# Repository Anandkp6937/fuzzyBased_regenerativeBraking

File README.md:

<h1 style="font-weight:bold">fuzzy logic based regenrative braking system</h1>

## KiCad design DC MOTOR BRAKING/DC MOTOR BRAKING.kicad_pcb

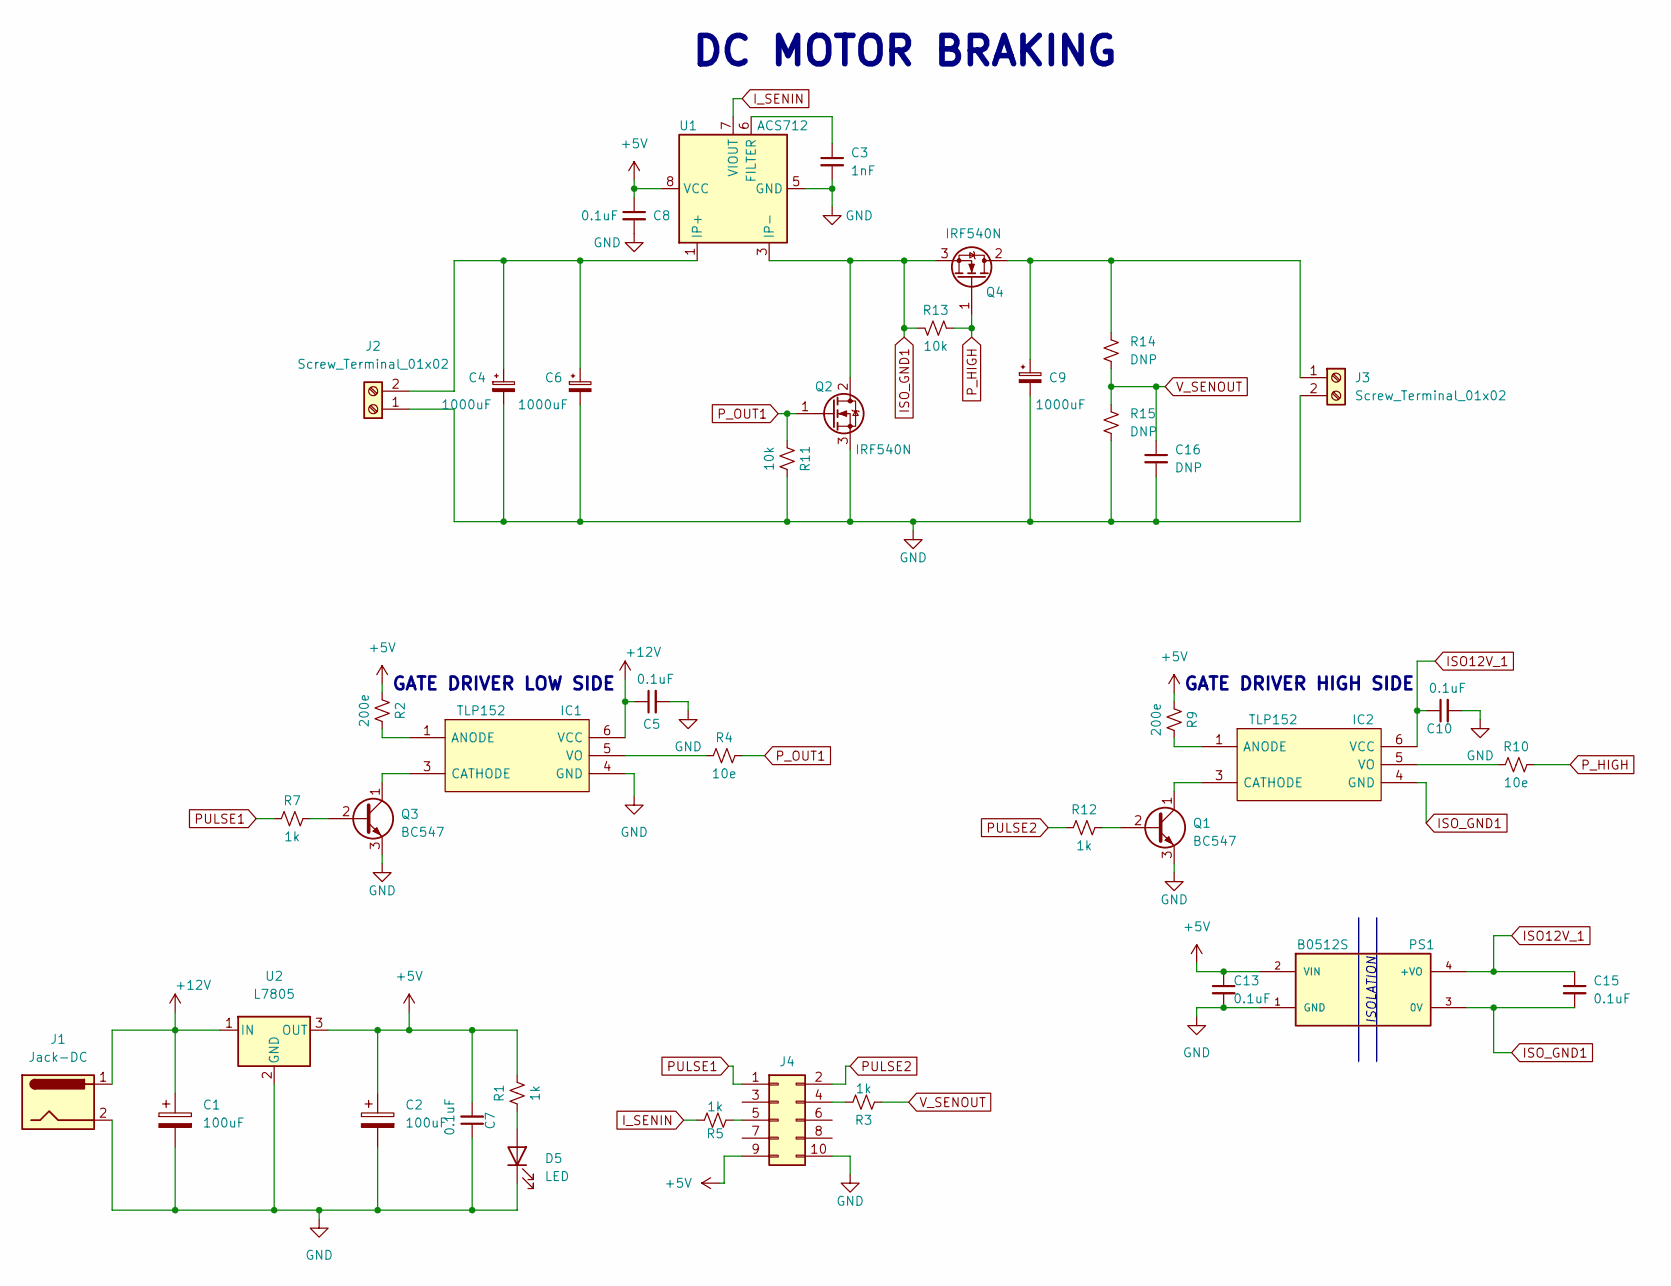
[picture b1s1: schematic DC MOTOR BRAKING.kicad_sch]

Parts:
C1: 100uF; CP_Radial_D6.3mm_P2.50mm
C2: 100uF; CP_Radial_D5.0mm_P2.50mm
C3: 1nF; C_0805_2012Metric_Pad1.18x1.45mm_HandSolder
C4, C6, C9: 1000uF; CP_Radial_D10.0mm_P5.00mm
C5, C7, C10, C13, C15: 0.1uF; C_Disc_D5.1mm_W3.2mm_P5.00mm
C8: 0.1uF; C_0805_2012Metric_Pad1.18x1.45mm_HandSolder
C16: DNP; C_Disc_D5.0mm_W2.5mm_P2.50mm
D5: LED; LED_D5.0mm
IC1, IC2: TLP152; SO-5_4.4x3.6mm_P1.27mm; Manufacturer_Part_Number TLP152
J1: Jack-DC; BarrelJack_Horizontal
J2, J3: Screw_Terminal_01x02; TerminalBlock_bornier-2_P5.08mm
J4: Conn_02x05_Odd_Even; IDC-Header_2x05_P2.54mm_Vertical
PS1: B0512S; CONV_B0512S-1WR3; PARTREV 2018.06.29-A/2
Q1, Q3: BC547; TO-92
Q2, Q4: IRF540N; TO-220
R1, R3, R5, R7, R12: 1k; 0.25W_resistor
R2, R9: 200e; 0.25W_resistor
R4, R10: 10e; 0.25W_resistor
R11, R13: 10k; 0.25W_resistor
R14, R15: DNP; 0.25W_resistor
U1: ACS712; SOIC-8_3.9x4.9mm_P1.27mm
U2: L7805; TO-220

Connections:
+5V: C2.1, C7.2, C8.1, C13.1, J4.9, PS1.2 (VIN), R1.2, R2.1, R9.1, U1.8 (VCC), U2.3 (OUT)
+12V: C1.1, C5.1, IC1.6 (VCC), J1.1, U2.1 (IN)
GND: C1.2, C2.2, C3.2, C4.2, C5.2, C6.2, C7.1, C8.2, C9.2, C10.2, C13.2, C16.2, D5.1 (K), IC1.4 (GND), J1.2, J2.1, J3.2, J4.10, PS1.1 (GND), Q1.3 (E), Q2.3 (S), Q3.3 (E), R11.1, R15.2, U1.5 (GND), U2.2 (GND)
ISO12V_1: C10.1, C15.1, IC2.6 (VCC), PS1.4 (+VO)
ISO_GND1: C15.2, IC2.4 (GND), PS1.3 (0V), Q2.2 (D), Q4.3 (S), R13.1, U1.3 (IP-), U1.4 (IP-)
I_SENIN: R5.2, U1.7 (VIOUT)
unnamed: D5.2 (A), R1.1
unnamed: IC1.1 (ANODE), R2.2
unnamed: IC1.3 (CATHODE), Q3.1 (C)
unnamed: IC1.5 (VO), R4.1
unnamed: IC2.1 (ANODE), R9.2
unnamed: IC2.3 (CATHODE), Q1.1 (C)
unnamed: IC2.5 (VO), R10.1
unnamed: C4.1, C6.1, J2.2, U1.1 (IP+), U1.2 (IP+)
unnamed: C9.1, J3.1, Q4.2 (D), R14.1
unnamed: J4.4, R3.2
unnamed: J4.5, R5.1
unnamed: Q1.2 (B), R12.2
unnamed: Q3.2 (B), R7.2
unnamed: C3.1, U1.6 (FILTER)
PULSE1: J4.1, R7.1
PULSE2: J4.2, R12.1
P_HIGH: Q4.1 (G), R10.2, R13.2
P_OUT1: Q2.1 (G), R4.2, R11.2
V_SENOUT: C16.1, R3.1, R14.2, R15.1

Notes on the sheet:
DC MOTOR BRAKING
GATE DRIVER HIGH SIDE
GATE DRIVER LOW SIDE
ISOLATION

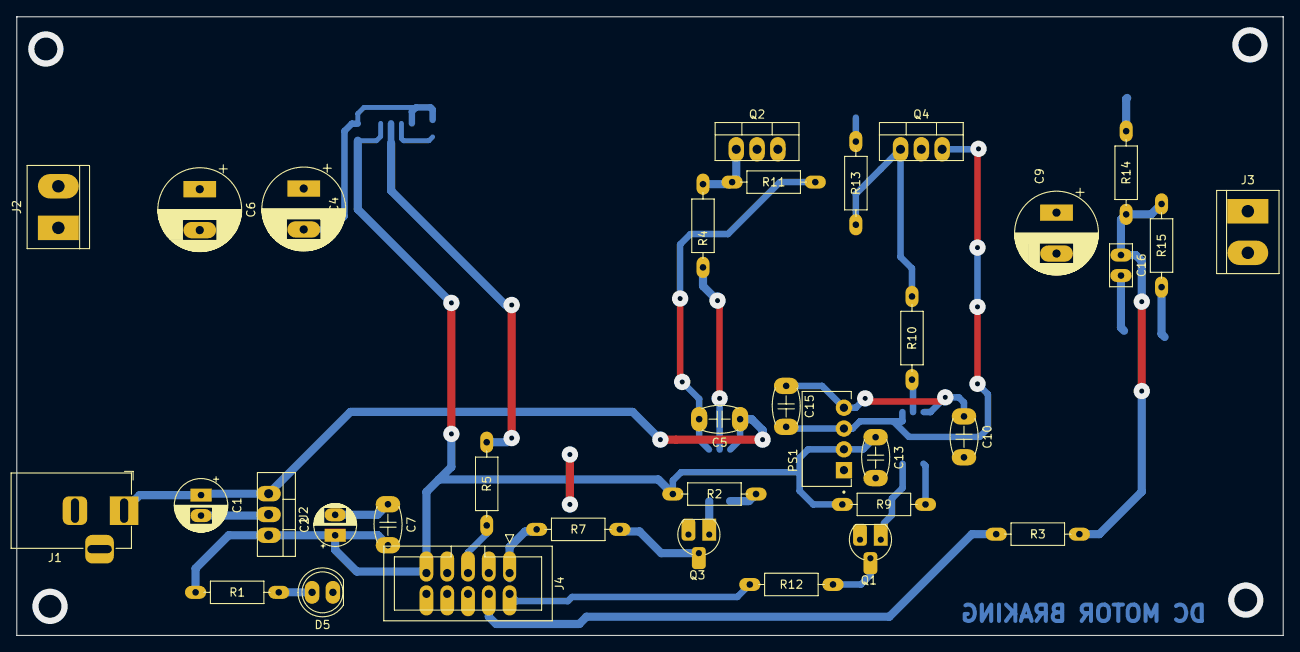
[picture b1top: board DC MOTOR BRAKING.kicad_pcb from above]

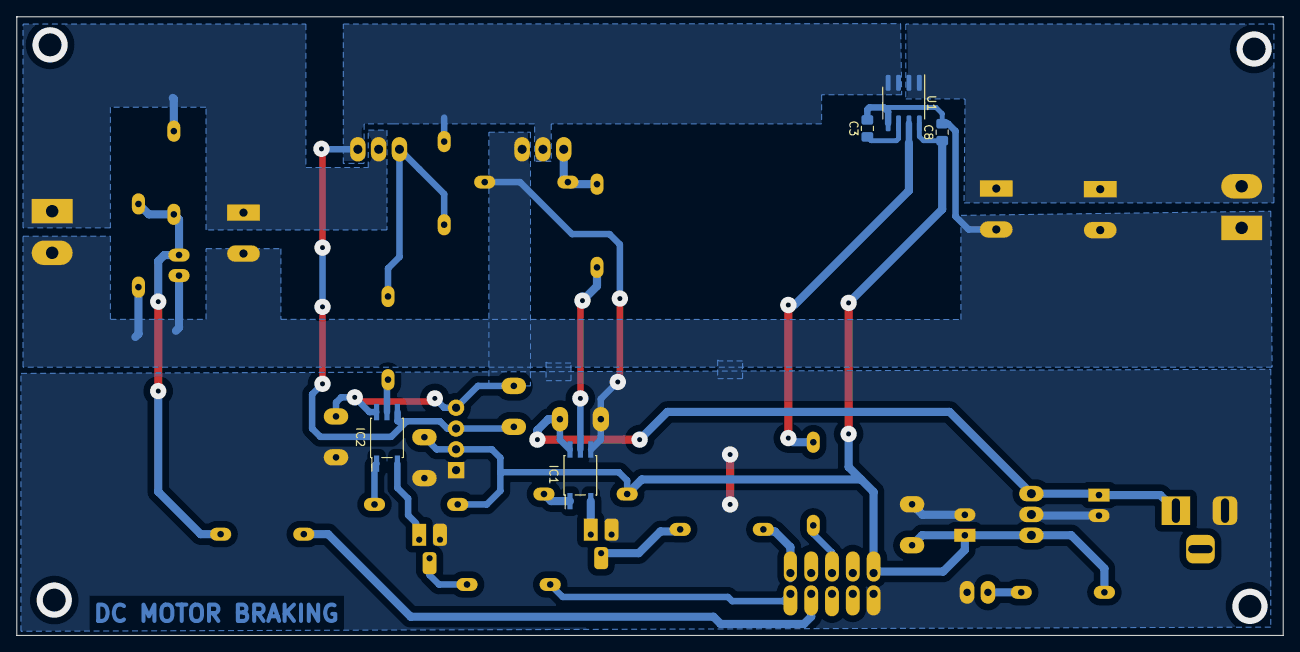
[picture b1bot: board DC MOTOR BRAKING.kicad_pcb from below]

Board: 2 copper layers, 154.7 x 75.6 mm, 40 parts (5 on the bottom side), 25 nets.

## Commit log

2024-04-25 Add files via upload
    added fuzzy rules
2024-04-25 updated title
